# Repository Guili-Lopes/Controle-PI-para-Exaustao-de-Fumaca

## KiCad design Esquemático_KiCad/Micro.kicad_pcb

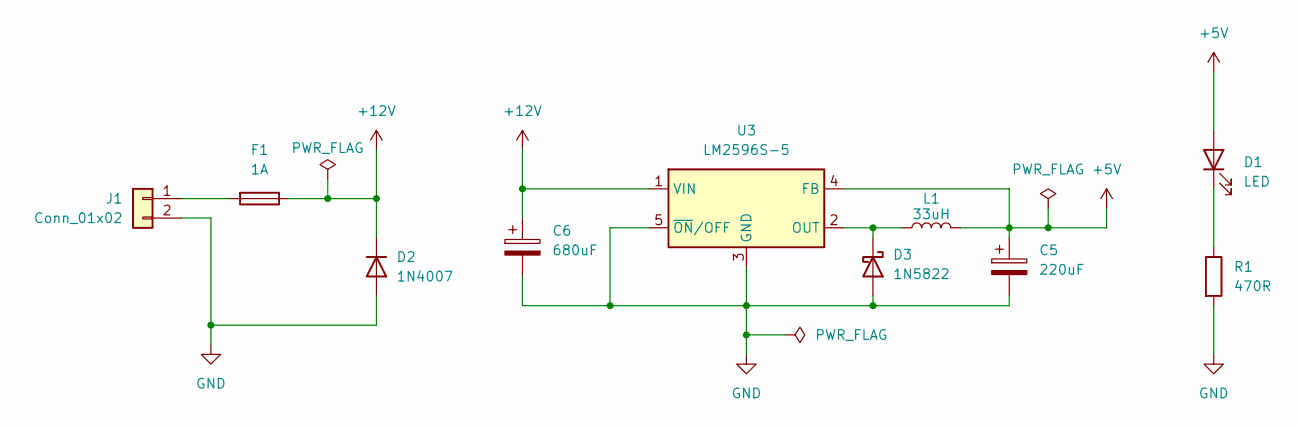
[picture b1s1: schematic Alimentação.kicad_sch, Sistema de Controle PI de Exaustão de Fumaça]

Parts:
C5: 220uF; CP_Radial_D10.0mm_P5.00mm
C6: 680uF; CP_Radial_D12.5mm_P5.00mm
D1: LED; LED_D5.0mm
D2: 1N4007; D_DO-41_SOD81_P10.16mm_Horizontal
D3: 1N5822; D_DO-201AD_P15.24mm_Horizontal
F1: 1A; Fuseholder_Cylinder-5x20mm_Schurter_0031_8201_Horizontal_Op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
J1: Conn_01x02; TerminalBlock_Phoenix_MKDS-1,5-2-5.08_1x02_P5.08mm_Horizont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
L1: 33uH; L_Radial_D18.0mm_P10.00mm
R1: 470R; R_Axial_DIN0207_L6.3mm_D2.5mm_P7.62mm_Horizontal
U3: LM2596S-5; TO-263-5_TabPin3

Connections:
+5V: C5.1, D1.2 (A), L1.2, U3.4 (FB); also elsewhere on the board
+12V: C6.1, D2.1 (K), F1.1, U3.1 (VIN); also elsewhere on the board
GND: C5.2, C6.2, D2.2 (A), D3.2 (A), J1.2, R1.2, U3.3 (GND), U3.5 (~ON/OFF); also elsewhere on the board
unnamed: D1.1 (K), R1.1
unnamed: D3.1 (K), L1.1, U3.2 (OUT)
unnamed: F1.2, J1.1

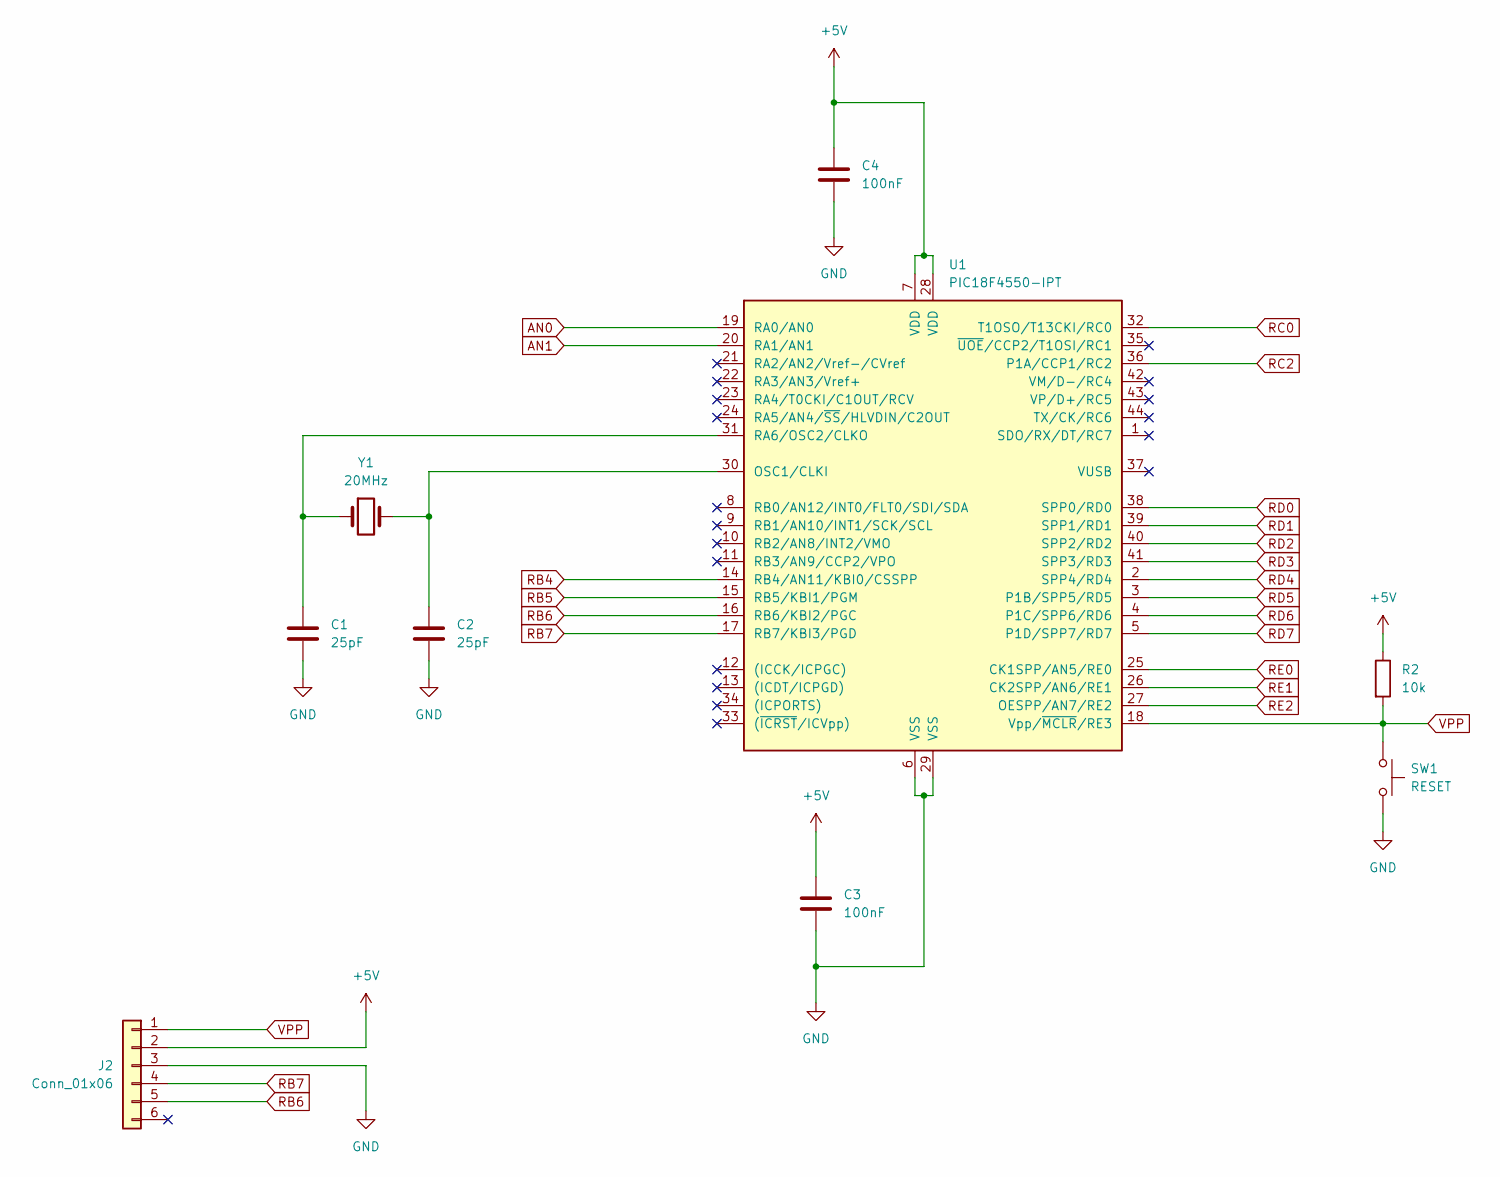
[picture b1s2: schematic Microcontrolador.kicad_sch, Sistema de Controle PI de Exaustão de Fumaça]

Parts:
C1, C2: 25pF; C_Disc_D5.0mm_W2.5mm_P2.50mm
C3, C4: 100nF; C_Disc_D5.0mm_W2.5mm_P2.50mm
J2: Conn_01x06; PinHeader_1x06_P2.54mm_Vertical
R2: 10k; R_Axial_DIN0207_L6.3mm_D2.5mm_P7.62mm_Horizontal
SW1: RESET; SW_PUSH_6mm_H5mm
U1: PIC18F4550-IPT; TQFP-44_10x10mm_P0.8mm
Y1: 20MHz; Crystal_HC49-U_Vertical

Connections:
+5V: C3.1, C4.1, J2.2, R2.1, U1.7 (VDD), U1.28 (VDD); also elsewhere on the board
AN0: U1.19 (RA0/AN0); also elsewhere on the board
AN1: U1.20 (RA1/AN1); also elsewhere on the board
GND: C1.2, C2.2, C3.2, C4.2, J2.3, SW1.2, U1.6 (VSS), U1.29 (VSS); also elsewhere on the board
unnamed: C2.1, U1.30 (OSC1/CLKI), Y1.2
unnamed: C1.1, U1.31 (RA6/OSC2/CLKO), Y1.1
RB4: U1.14 (RB4/AN11/KBI0/CSSPP); also elsewhere on the board
RB5: U1.15 (RB5/KBI1/PGM); also elsewhere on the board
RB6: J2.5, U1.16 (RB6/KBI2/PGC)
RB7: J2.4, U1.17 (RB7/KBI3/PGD)
RC0: U1.32 (T1OSO/T13CKI/RC0); also elsewhere on the board
RC2: U1.36 (P1A/CCP1/RC2); also elsewhere on the board
RD0: U1.38 (SPP0/RD0); also elsewhere on the board
RD1: U1.39 (SPP1/RD1); also elsewhere on the board
RD2: U1.40 (SPP2/RD2); also elsewhere on the board
RD3: U1.41 (SPP3/RD3); also elsewhere on the board
RD4: U1.2 (SPP4/RD4); also elsewhere on the board
RD5: U1.3 (P1B/SPP5/RD5); also elsewhere on the board
RD6: U1.4 (P1C/SPP6/RD6); also elsewhere on the board
RD7: U1.5 (P1D/SPP7/RD7); also elsewhere on the board
RE0: U1.25 (CK1SPP/AN5/RE0); also elsewhere on the board
RE1: U1.26 (CK2SPP/AN6/RE1); also elsewhere on the board
RE2: U1.27 (OESPP/AN7/RE2); also elsewhere on the board
VPP: J2.1, R2.2, SW1.1, U1.18 (Vpp/~MCLR/RE3)

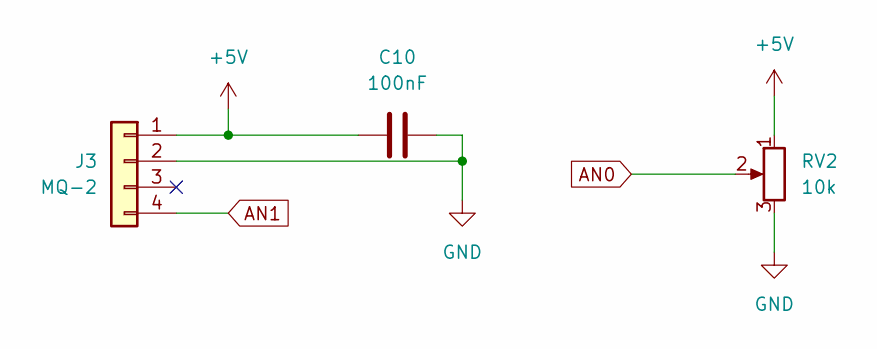
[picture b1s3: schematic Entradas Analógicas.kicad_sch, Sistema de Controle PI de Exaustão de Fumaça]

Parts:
C10: 100nF; C_Disc_D5.0mm_W2.5mm_P2.50mm
J3: MQ-2; PinHeader_1x04_P2.54mm_Vertical
RV2: 10k; Potentiometer_Bourns_3296W_Vertical

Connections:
+5V: C10.1, J3.1, RV2.1; also elsewhere on the board
AN0: RV2.2; also elsewhere on the board
AN1: J3.4; also elsewhere on the board
GND: C10.2, J3.2, RV2.3; also elsewhere on the board

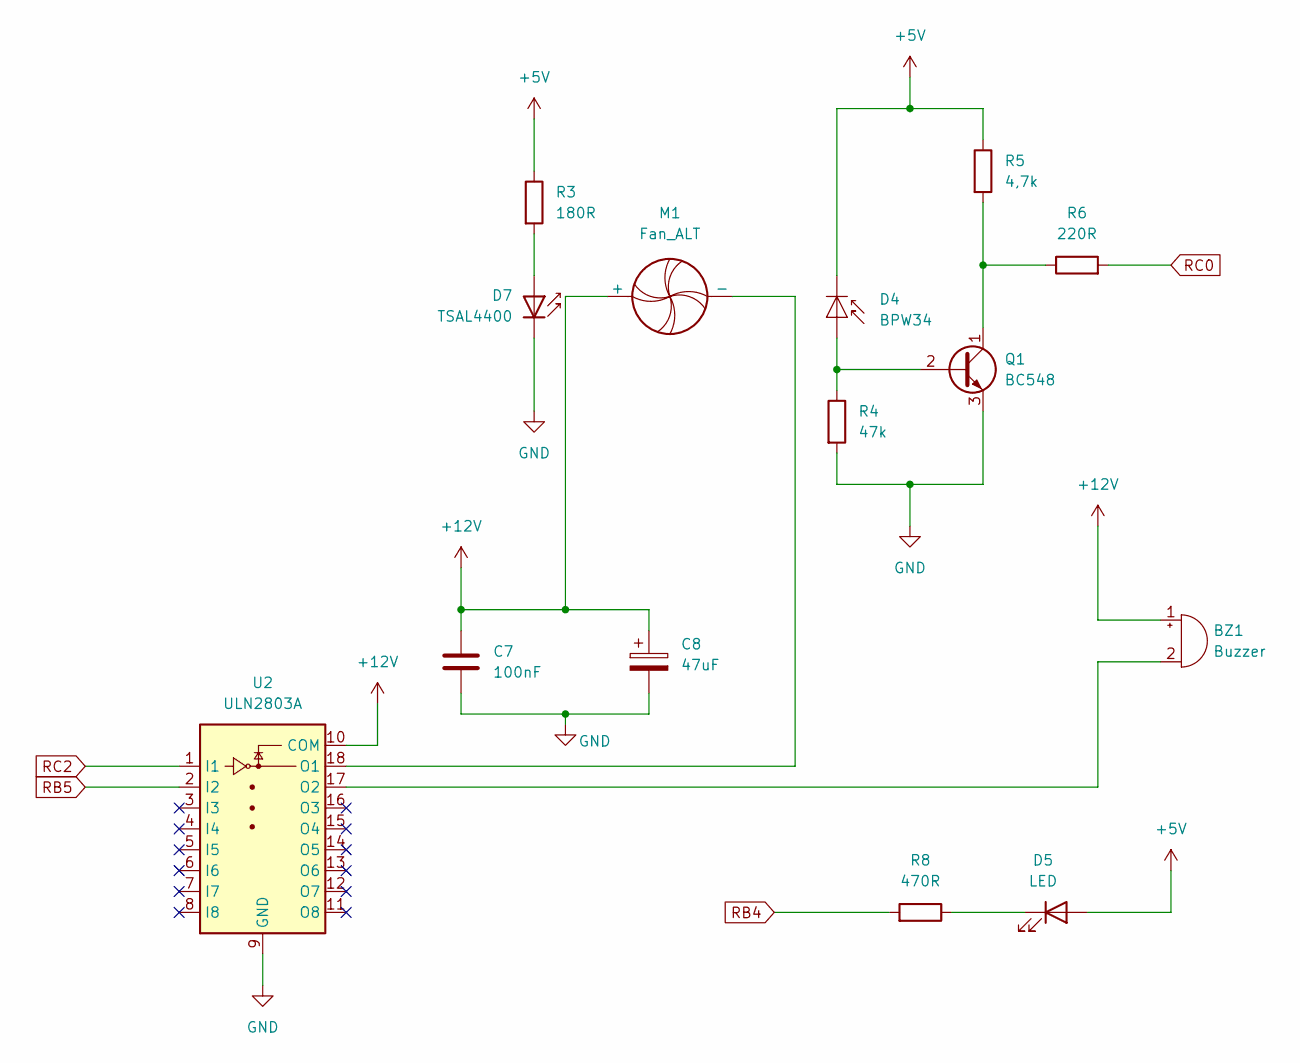
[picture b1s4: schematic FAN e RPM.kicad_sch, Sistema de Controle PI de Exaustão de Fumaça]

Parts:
BZ1: Buzzer; Buzzer_12x9.5RM7.6
C7: 100nF; C_Disc_D5.0mm_W2.5mm_P2.50mm
C8: 47uF; CP_Radial_D5.0mm_P2.00mm
D4: BPW34; Osram_DIL2_4.3x4.65mm_P5.08mm
D5: LED; LED_D5.0mm
D7: TSAL4400; LED_D3.0mm_IRBlack
M1: Fan_ALT; TerminalBlock_Phoenix_MKDS-1,5-2-5.08_1x02_P5.08mm_Horizont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
Q1: BC548; TO-92_Inline
R3: 180R; R_Axial_DIN0207_L6.3mm_D2.5mm_P7.62mm_Horizontal
R4: 47k; R_Axial_DIN0207_L6.3mm_D2.5mm_P7.62mm_Horizontal
R5: 4,7k; R_Axial_DIN0207_L6.3mm_D2.5mm_P7.62mm_Horizontal
R6: 220R; R_Axial_DIN0207_L6.3mm_D2.5mm_P7.62mm_Horizontal
R8: 470R; R_Axial_DIN0207_L6.3mm_D2.5mm_P7.62mm_Horizontal
U2: ULN2803A; DIP-18_W7.62mm

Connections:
+5V: D4.1 (K), D5.2 (A), R3.1, R5.1; also elsewhere on the board
+12V: BZ1.1 (+), C7.1, C8.1, M1.1 (+), U2.10 (COM); also elsewhere on the board
GND: C7.2, C8.2, D7.1 (K), Q1.3 (E), R4.2, U2.9 (GND); also elsewhere on the board
unnamed: BZ1.2 (-), U2.17 (O2)
unnamed: D4.2 (A), Q1.2 (B), R4.1
unnamed: D5.1 (K), R8.1
unnamed: D7.2 (A), R3.2
unnamed: M1.2 (-), U2.18 (O1)
unnamed: Q1.1 (C), R5.2, R6.1
RB4: R8.2; also elsewhere on the board
RB5: U2.2 (I2); also elsewhere on the board
RC0: R6.2; also elsewhere on the board
RC2: U2.1 (I1); also elsewhere on the board

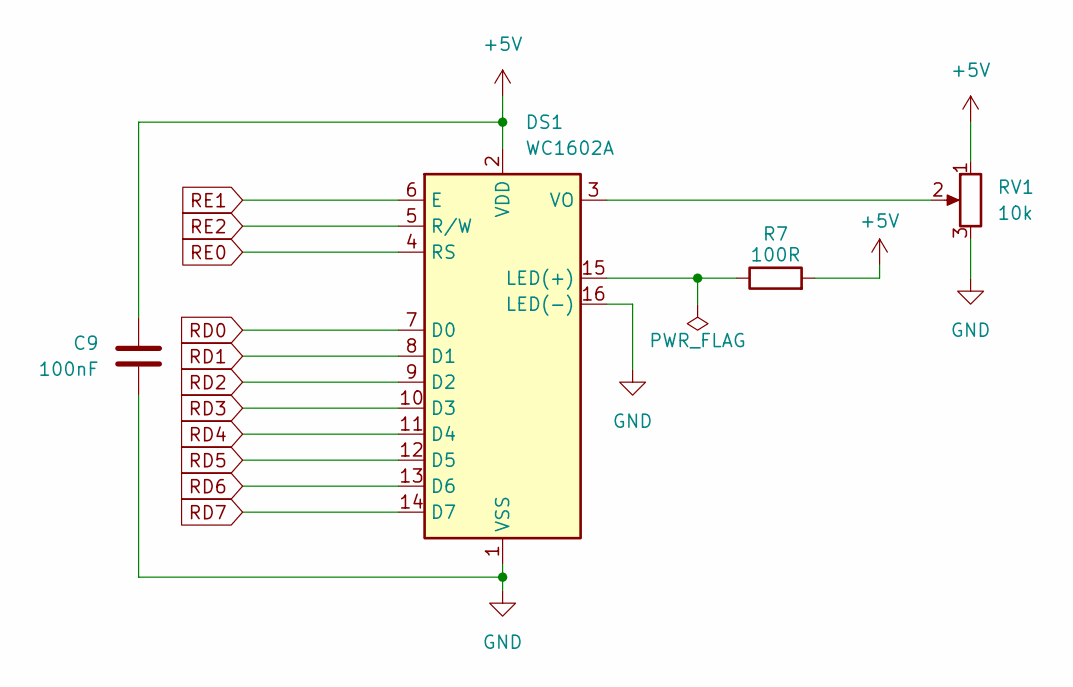
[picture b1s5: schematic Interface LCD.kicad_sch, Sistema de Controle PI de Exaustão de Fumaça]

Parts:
C9: 100nF; C_Disc_D5.0mm_W2.5mm_P2.50mm
DS1: WC1602A
R7: 100R; R_Axial_DIN0207_L6.3mm_D2.5mm_P7.62mm_Horizontal
RV1: 10k; Potentiometer_Bourns_3296W_Vertical

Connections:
+5V: C9.1, DS1.2 (VDD), R7.2, RV1.1; also elsewhere on the board
GND: C9.2, DS1.1 (VSS), DS1.16 (LED(-)), RV1.3; also elsewhere on the board
unnamed: DS1.15 (LED(+)), R7.1
unnamed: DS1.3 (VO), RV1.2
RD0: DS1.7 (D0); also elsewhere on the board
RD1: DS1.8 (D1); also elsewhere on the board
RD2: DS1.9 (D2); also elsewhere on the board
RD3: DS1.10 (D3); also elsewhere on the board
RD4: DS1.11 (D4); also elsewhere on the board
RD5: DS1.12 (D5); also elsewhere on the board
RD6: DS1.13 (D6); also elsewhere on the board
RD7: DS1.14 (D7); also elsewhere on the board
RE0: DS1.4 (RS); also elsewhere on the board
RE1: DS1.6 (E); also elsewhere on the board
RE2: DS1.5 (R/W); also elsewhere on the board

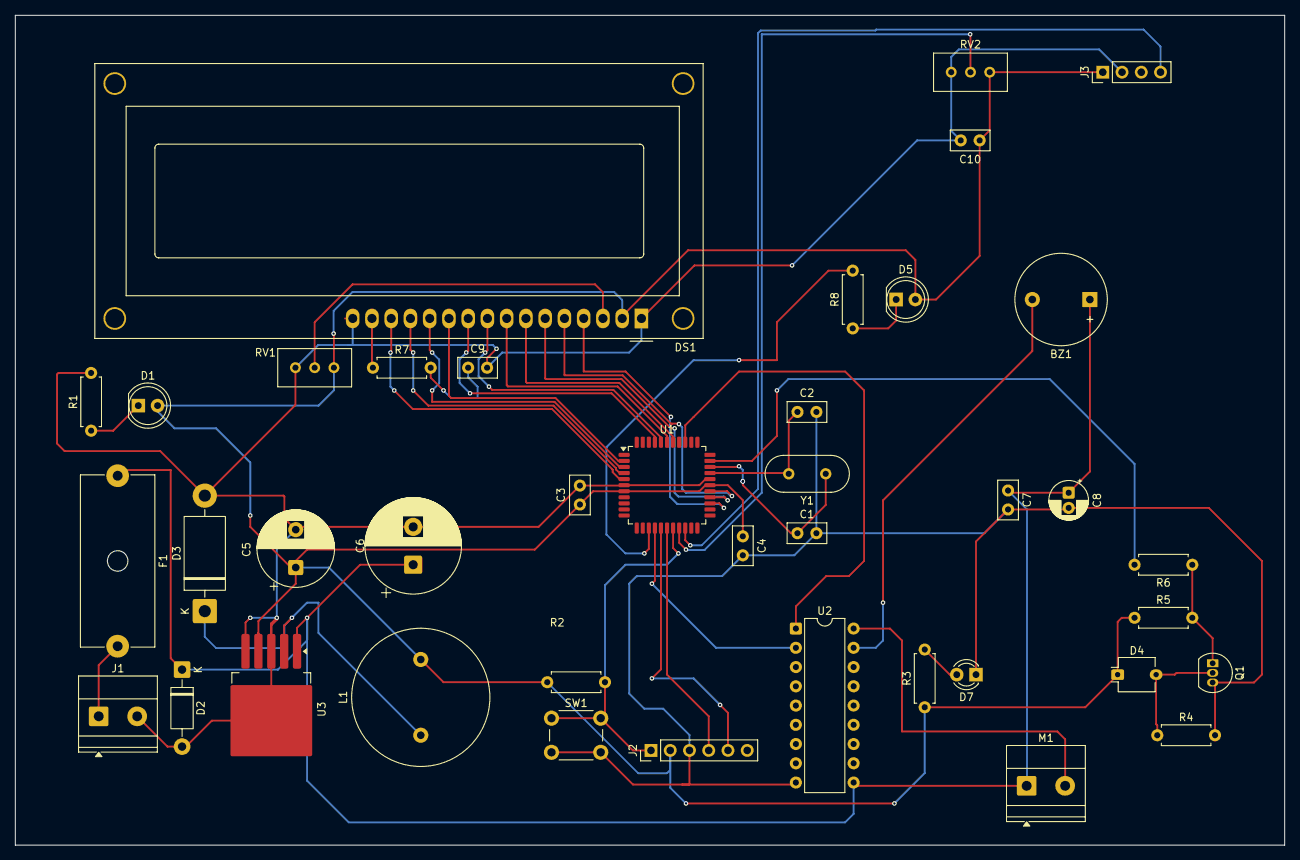
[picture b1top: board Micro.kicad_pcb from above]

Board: 2 copper layers, 167.5 x 109.5 mm, 40 parts (0 on the bottom side), 36 nets.

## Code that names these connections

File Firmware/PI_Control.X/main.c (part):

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#define ADC_POT_CONFIG 0b00000001           // CHS=0000 -> AN0; ADON=1
#define ADC_SENSOR_CONFIG 0b00000101        // CHS=0001 -> AN1; ADON=1
#define ADC_GO_MASK 0b00000010              // GO/DONE: inicia/conclui conversao
#define TACOGRAFO_IO TRISCbits.TRISC0       // RC0/T13CKI, entrada de pulsos
#define TACOGRAFO_PINO PORTCbits.RC0        // Apenas leitura digital
#define FAN_IO TRISCbits.TRISC2             // RC2/CCP1, saida PWM
#define FAN_LATCH LATCbits.LATC2           

// LCD alfanumerico 16x2, barramento de dados de 8 bits
#define LCD_DATA LATD               // D7..D0 em RD7..RD0
#define LCD_DATA_IO TRISD
#define LCD_RS LATEbits.LATE0       // RE0: 0=comando, 1=dado
#define LCD_EN LATEbits.LATE1       // RE1: pulso de habilitacao
#define LCD_RW LATEbits.LATE2       // RE2: 0=escrita, 1=leitura

// Sinalização de nível alto de fumaça com buzzer e LED
#define LED_IO TRISBbits.TRISB4         // RB4 como saída digital
#define LED_LATCH LATBbits.LATB4
#define BUZZER_IO TRISBbits.TRISB5     // RB5 como saída digital
#define BUZZER_LATCH LATBbits.LATB5
#define BUZZER_ON 0b1
#define BUZZER_OFF 0b0
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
